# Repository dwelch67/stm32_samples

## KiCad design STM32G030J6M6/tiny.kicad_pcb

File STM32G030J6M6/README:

1       8
2 VCC   7
3 GND   6 PA10 RX
4       5 PA9  TX

This is the hookup to use the UART bootloader.  The documentation
is unclear.  It shows [PA9] and [PA10] but then in the pin
descriptions does not show these signals as having pins.  But this
happened to work.

This part does let you use the UART bootloader if the flash is empty
otherwise there is a security deal that blocks it, you are expected
to use SWD.  But if you use progstm (the one in this directory)
to program the part with the RUN_ME_FIRST binary.  it will change the
bit from default so that you can use boot0 and continue to use
the UART bootloader.  I assume this is the new norm, and/or the
bootloader will just go away some day.

After RUN_ME_FIRST remove power to the chip for it to work.

see the tiny.kicad_pcb board, costs like $1.50 for three at
oshpark.

I have an led on PB13

tiny2.kicad_pcb
using this part
STM32G030J6M6
these cute little switches they dont look like the picture but they
fit/work just fine.
MCSLPT4644B1TR
A 10K (0603) for the boot0 pull up, and then a 0603 led and resistor.

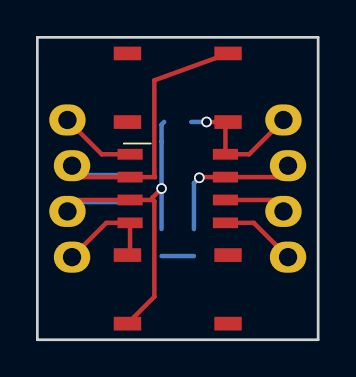
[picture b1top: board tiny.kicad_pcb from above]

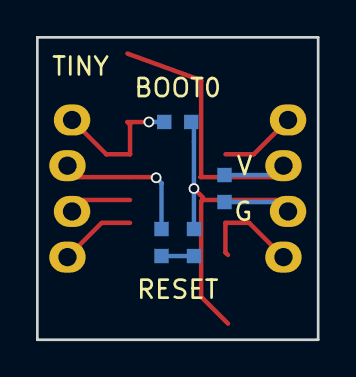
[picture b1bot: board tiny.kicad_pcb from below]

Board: 2 copper layers, 15.6 x 16.8 mm, 6 parts (4 on the bottom side), 4 nets.

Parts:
BOOT0: BUTTON4_SMD
C: C_0603
L: L_0603
R: R_0603
R#2: R_0603
RESET: BUTTON4_SMD

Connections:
boot0: BOOT0.BOOT, R.BOOT
gled: L.GLED, R#2.GLED
gnd: C.2, R.GND, R#2.GND, RESET.GND
vcc: BOOT0.VCC, C.1

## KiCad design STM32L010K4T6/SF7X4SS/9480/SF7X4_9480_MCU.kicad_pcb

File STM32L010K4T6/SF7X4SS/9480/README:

The attached kicad pcb file is what I used for this project.

SF7X4_9480.kicad_pcb
SF7X4_9480_MCU.kicad_pcb

Based around these seven segment displays from sparkfun.

https://www.sparkfun.com/products/9480

Three boards total, the first one is just the leds and resistors.
The MCU board drives the leds, with numbers00 it takes a string
from the uart and displays four numbers based on that.  A third
board has a gps and extracts the time (very accurate and no
need to set the thing) and creates the string to send to the
mcu board.

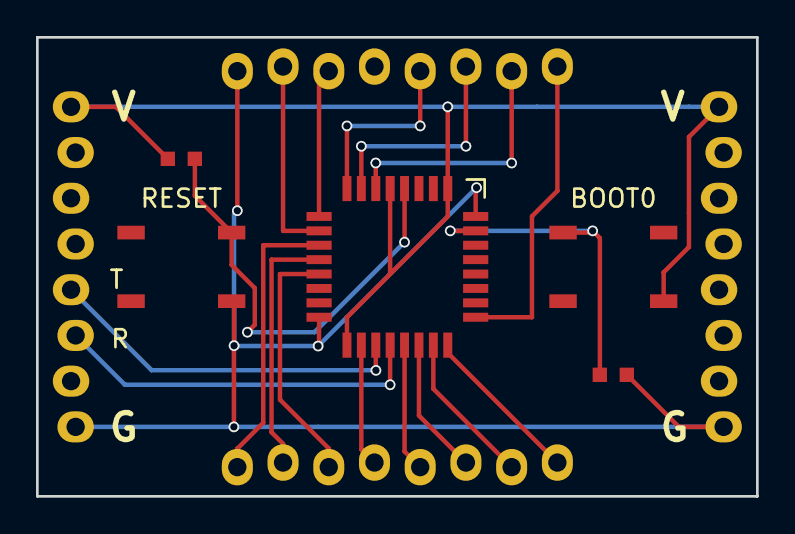
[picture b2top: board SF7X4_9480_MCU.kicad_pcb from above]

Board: 2 copper layers, 40.0 x 25.5 mm, 5 parts (0 on the bottom side), 4 nets.

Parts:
BOOT0: BUTTON4_SMD
LQFP32: STM32_LQFP32
R: R_0603
R#2: R_0603
RESET: BUTTON4_SMD

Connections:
/boot0: BOOT0.3, LQFP32.BOOT, R#2.1
/gnd: LQFP32.GND, R#2.2, RESET.2
/reset: LQFP32.RST, R.2, RESET.4
/vcc: BOOT0.2, LQFP32.3.3, R.1

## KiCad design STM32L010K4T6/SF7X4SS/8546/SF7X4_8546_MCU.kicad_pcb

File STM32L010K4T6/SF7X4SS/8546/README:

The attached kicad pcb file is what I used for this project.

SF7X4_8546.kicad_pcb
SF7X4_8546_MCU.kicad_pcb

Based around these seven segment displays from sparkfun.

https://www.sparkfun.com/products/8546

Three boards total, the first one is just the leds and resistors.
The MCU board drives the leds, with numbers00 it takes a string
from the uart and displays four numbers based on that.  A third
board has a gps and extracts the time (very accurate and no
need to set the thing) and creates the string to send to the
mcu board.

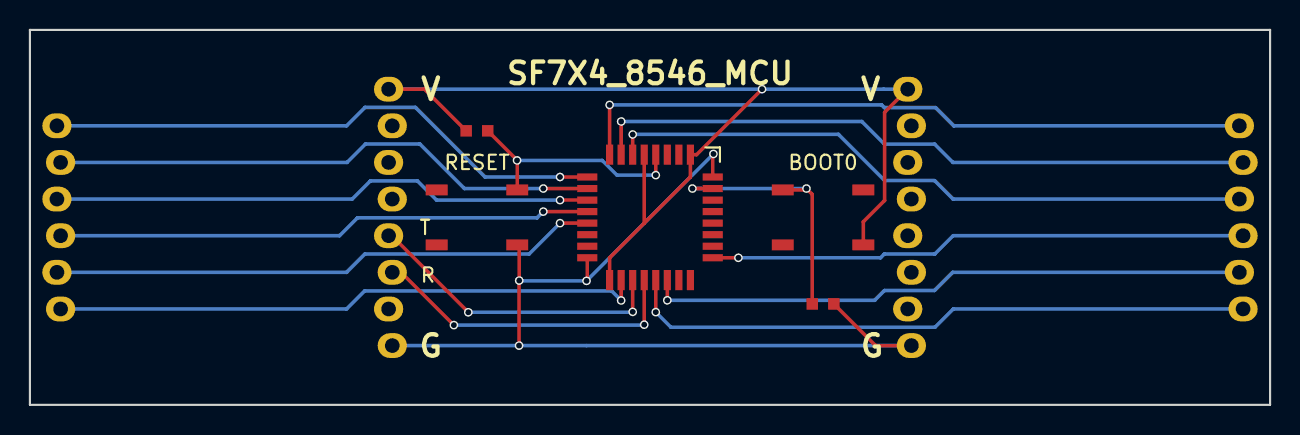
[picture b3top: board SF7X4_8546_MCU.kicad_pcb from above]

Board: 2 copper layers, 86.0 x 26.0 mm, 6 parts (1 on the bottom side), 16 nets.

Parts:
8546: SF7X4_8546_mate
BOOT0: BUTTON4_SMD
LQFP32: STM32_LQFP32
R: R_0603
R#2: R_0603
RESET: BUTTON4_SMD

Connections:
/boot0: BOOT0.3, LQFP32.BOOT, R#2.1
/gnd: LQFP32.GND, R#2.2, RESET.2
/led0: 8546.V0, LQFP32.PA0
/led1: 8546.V1, LQFP32.PA15
/led2: 8546.V2, LQFP32.PA5
/led3: 8546.V3, LQFP32.PA6
/ledA: 8546.A, LQFP32.PA4
/ledB: 8546.B, LQFP32.PA3
/ledC: 8546.C, LQFP32.PA8
/ledD: 8546.D, LQFP32.PA12
/ledE: 8546.E, LQFP32.PA11
/ledF: 8546.F, LQFP32.PA2
/ledG: 8546.G, LQFP32.PA1
/ledP: 8546.P, LQFP32.PA7
/reset: LQFP32.RST, R.2, RESET.4
/vcc: BOOT0.2, LQFP32.3.3, R.1

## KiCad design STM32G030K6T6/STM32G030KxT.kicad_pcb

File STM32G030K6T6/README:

This is the second one of these parts I have dealt with.  I expect
this to be the new norm.

First off THE PINOUT IS DIFFERENT, from older parts, even better
power is now ground or something like that, so make sure you build
your board to the datasheet for this part, not other STM32 parts.

Second you get ONE SHOT at serial bootloader programming, a virgin
part will go into the bootloader.  But once programmed with a
vector table it uses the internal option register to determine
boot mode which defaults to NOT using the BOOT0 pin. So load and
run the RUN_ME_FIRST program, then power cycle the chip not just
reset, and now you can use the BOOT0 pin like all the STM32s up to
this point.  Failing to do that you have to use an SWD debugger
to get into the chip.

Third you cant necessarily just poke at the flash registers from
the debugger, but you can load programs into ram that can.  So if you
get stuck not being able to load using the serial bootloader then
you need to write programs that you load and run from ram that
do whatever.  I was not able to erase the flash, but was able
to set the option register correctly using a ram based version
of RUN_ME_FIRST.  Remember to power cycle after changing that
register.

If you dont mess up then if you use progstm to load RUN_ME_FIRST
(and then power cycle dont just reset) you can in use the serial
bootloader to load programs (progstm) and use the boot0 and reset
buttons to put it back in the bootloader to try again. I have
confirmed this on virgin parts.

Basically RUN_ME_FIRST using progstm, then you can use progstm from
there on out and not need a swd/jtag debugger for this part.

Not that not all of my progstms are created equal, there are different
revisions of bootloaders that come with these parts so the one in
this parts directory tree goes with this part.

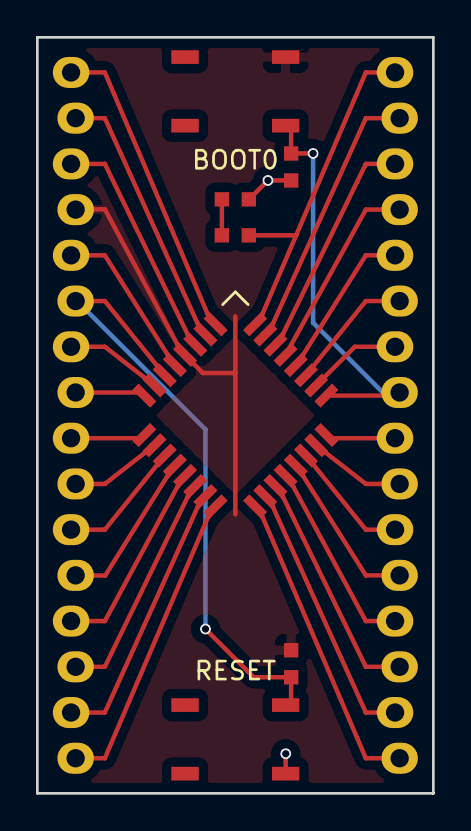
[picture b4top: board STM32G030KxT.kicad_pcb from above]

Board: 2 copper layers, 22.0 x 42.0 mm, 7 parts (0 on the bottom side), 6 nets.

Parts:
BOOT0: BUTTON4_SMD
L: L_0603
LQFP32: STM32G030KxT_LQFP32
R: R_0603
R#2, R#3: R_0603
RESET: BUTTON4_SMD

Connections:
/boot0: BOOT0.3, LQFP32.PA14, R.2
/gnd: L.2, LQFP32.GND, R.1, RESET.2
/nrst: LQFP32.RST, R#2.1, RESET.4
/pb8: LQFP32.PB8, R#3.2
/vcc: BOOT0.1, LQFP32.3.3, R#2.2
/x0: L.1, R#3.1

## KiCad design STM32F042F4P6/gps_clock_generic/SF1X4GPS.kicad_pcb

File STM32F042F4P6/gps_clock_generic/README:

This is a generic NMEA parser intended for GPS based clocks the
specific initial board is SF1X4GPS.kicad_pcb which uses the PA6H
GTOP Ladybird 1 GPS which works pretty good indoors significantly better
than modules from before.  They are pricy at $20 each so have some
BN-220s that dont solder down on this board but work at like $15 each.

Hoping for something closer to $10 with an antenna that I can solder
down that works great indoors.

This board was designed to mate with SF1X4MCU2.kicad_pcb which uses
an STM32F042L010K4T6 so see that directory for more.

I have reused this nmea code many times now, works great.

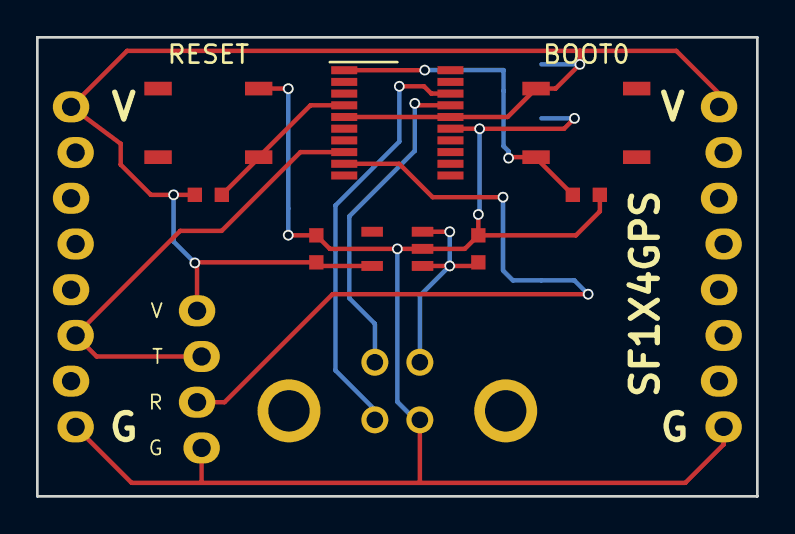
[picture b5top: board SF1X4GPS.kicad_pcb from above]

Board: 2 copper layers, 40.0 x 25.5 mm, 10 parts (1 on the bottom side), 8 nets.

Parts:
AP2112: AP2112
BOOT0: BUTTON4_SMD
C: C_0603
C#2: C_0603
PA6H: GPS; PA6H
R: R_0603
R#2: R_0603
RESET: BUTTON4_SMD
STM32: STM32F042F4; STM32
USB: Wurth_61400413321_usb

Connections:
/boot0: BOOT0.1, R.1, STM32.BOOT
/gnd: AP2112.GND, C.2, C#2.2, PA6H.GND, R.2, RESET.4, STM32.GND, USB.G
/nmea: PA6H.TX, STM32.PA3
/reset: R#2.2, RESET.2, STM32.NRST
/usbdm: STM32.PA11, USB.-
/usbdp: STM32.PA12, USB.+
/vcc: AP2112.VOUT, BOOT0.3, C#2.1, PA6H.VCC, R#2.1, STM32.VCC
/vin: AP2112.EN, AP2112.VIN, C.1, USB.V

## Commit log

2014-11-10 starting to populate this
2014-11-10 worked on STM32F0 readme and pulling in examples
2014-11-10 moving in more examples
2014-11-10 moving over the rest of the stm32f0d examples
2014-11-21 adding ssd1306 example for the stm32f0 discovery
2014-11-22 adding an example for a 4 digit 7 segment display
2014-11-22 adding ssd1306 examples
2014-11-22 adding ssd1306 example
2014-11-22 bugfix
2014-11-22 still trying
2014-11-25 I guess I had the detection right
2014-12-03 adding blinker examples for stm32f0 nucleo board
2014-12-03 adding uart examples for stm32 f030r8 nucleo
2014-12-03 readme changes
2014-12-04 adding a few NUCLEO-F401RE examples
2014-12-04 didnt save a couple of files before committing
2014-12-05 fixing flash latency when clock is faster
2014-12-05 adding real time clock example
2014-12-08 more NULCEO-F401RE examples
2014-12-09 adding ds3231 example
2014-12-31 disable overrun on rx
2014-12-31 another nmea parser
2015-10-22 adding STM32F031F4P6 directory and some examples
2015-10-22 if boot0 is a 1 then you can use the serial bootloader
2015-10-23 forgot readme
2015-11-11 adding stuff for my own breakout board
2015-11-12 both leds blink now
2015-11-14 updating readmes
2015-11-18 adding stm32l053 discovery initial examples
2015-11-19 adding a couple of blinker examples to DWSTM32
2015-11-19 adding a couple more DWSTM32 examples (STM32F0)
2015-11-20 blinker04 example uses the pll to get to 48Mhz
2015-11-20 more uart stuff
2015-11-20 fixing makefiles
2015-11-21 added uart based stuff, cleaned up things
2015-11-21 added to readme
2015-11-21 adding a couple more examples, interesting benchmark
2015-11-21 updating benchmark example
2015-12-11 working with the e paper display on the stm32l0 discovery
2015-12-11 epaper display sample with some font data drawing letters
2015-12-12 adding gps_clock using the e-paper display
2015-12-14 nokia 5110 screen example
2015-12-16 adding an example for the Nordic nRF24L01+
2015-12-17 adding simple pulse measurement example
2016-01-07 adding NUCLEO-F031K6 examples
2016-01-09 adding examples for the NUCLEO-F411RE
2016-01-09 documentation updates
2016-01-09 typo
2016-01-12 adding uart02 example
2016-01-12 adding fixing uart2 example
2016-01-15 fixing readme again
2016-01-15 adding uart03 examples, uses internal 16Mhz instead of external 8MHz.
2016-01-15 adding uart04 example, uses pll to get to 16Mhz.
2016-03-25 built a little charlieplexed led board, will push the board design file later, it is on another computer.
2016-03-26 adding board file for charlieplexed led board
2016-03-26 so fixes and improvements and additional examples for the charlieplexed led board.
2016-04-02 adding a gps_clock and fixing bugs
2016-04-06 adding gps_clock02. glows the other leds removing/reducing the problem reading the bits
2016-04-13 adding examples for another stm32 board I made this time a 32 pin quad flat pack.
2016-04-13 adding blinker04
2016-04-13 adding uart01 example
2016-04-13 adding uart03 example
2016-04-16 forgot to slow the flash down!
2016-04-16 forgot to slow the flash down first!
2016-04-16 fixing flash linker script to allow for ram
2016-04-16 fixing linker script to allow for ram
2016-04-16 another breakout board
2016-05-04 adding systick interrupt example
2016-05-05 adding int02 example using timer 14
2016-05-05 adding blinker05 example using TIM2
2016-05-09 adding blinker06 example
2016-05-10 adding PWM example
2016-05-10 adding blinker08 example, demonstrates the IRTIM output, which NANDs TIM16 and TIM17
2016-05-10 adding two hardware spi examples
2016-05-16 stm32f7 board first example
2016-07-14 adding stm32f7 examples
2016-07-14 updating DWT example on cortex-m7. bug in the TRM documentation
2016-09-01 updating uart01 to use /dev/ttyACM0
2016-09-01 adding stepper01
2016-09-15 adding nokia example using hw spi instead of bit banged
2016-09-15 nokia with text example
2016-09-24 starting STM32F103C8T6 samples
2016-09-24 updating and adding stm32f1x examples
2016-09-24 examples using the PLL to get to 72Mhz. more cleanup
2016-09-26 confirmed the write protect problem, added progstm to help with that
2016-09-26 more info
2016-09-28 updating readme with j-link info
2016-09-28 updating readme about jlink swd
2016-09-29 working on something
2016-10-02 adding particle photon bare metal, uses an stm32f2
2016-10-04 adding an example for an HT1621B driven display
2016-10-05 adding another gps clock
2016-10-10 blinking leds
2016-10-15 ws2812b neopixel examples
2016-10-17 neopixel/ws2812b example for another board
2016-10-18 another mcu driving neopixel/ws2812b
2016-10-18 improving the timing
2016-10-19 adding rtc01 example
2016-10-19 updating rtc01, adding rtc02
2016-10-19 rtc clock
2016-10-20 horrible accuracy, trying something...
2016-10-21 npix02
2016-10-21 rtc wip
2016-10-26 trying to sort out the 16 minutes per day error I am seeing
2016-10-30 rtc04 still figuring out accuracy of the rtc
2016-10-31 more work on rtc based clock
2016-11-04 adding uartdev
2016-11-06 daylight savings time adjustment
2016-11-25 adding stuff for this chip, whole purpose was to make an lcd clock.
2016-11-29 update on how the lcd panels are reacting
2016-11-30 tmp102
2016-12-08 adding interrupt examples
2016-12-11 adding examples for a very inexpensive ebay board
2016-12-13 adding STM32L011F4P6 ultra low power mcu examples
2016-12-14 work on STM32L0x1
2016-12-20 interrupt based blinkers
2017-01-12 second times a charm. able to program through the serial bootloader
2017-01-13 lowering the power some
2017-01-13 lowering vcore
2017-01-25 adding ht1621 based display examples
2017-01-27 back to playing with an oled display
2017-01-31 more ssd1306 fun, learned a couple new things
2017-02-01 slightly better centering on the numbers
2017-02-11 adding a simple bootloader
2017-02-11 adding bootloader
2017-03-05 adding some openocd files
2017-03-08 adding openocd files
2017-03-08 adding some examples for the STM32F030F4P6 (cheap ebay board)
2017-03-08 adding blinker03 using HSE clock
2017-03-14 adding stm32f103 interrupt example
2017-03-28 adding cortex-m4 NVIC example
2017-04-03 first NUCLEO-F767ZI examples
2017-04-04 more STM32F767ZI examples
2017-04-04 another example
2017-04-09 reading cpuid registers
2017-04-09 messed with the fpu a little, checked the fpu features registers
2017-07-11 simple charlieplex board tester
2017-10-09 using int02 as the base line, 20ua
2017-10-19 adding example for sharp memory lcd
2018-02-02 someone on stackoverflow found this interesting bug in gnu assembler.
2018-04-05 adding a gps based clock
2018-08-09 added a Analog to Digital conversion example using ADC1. tmpsensor_internal.c uses the built in temprature sensor on channel 16, and adc01.c uses any analog sensor connected to PB1. No real conversio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
2019-09-21 single display that blinks 4 times instead of four displays
2020-06-15 correcting terminology
